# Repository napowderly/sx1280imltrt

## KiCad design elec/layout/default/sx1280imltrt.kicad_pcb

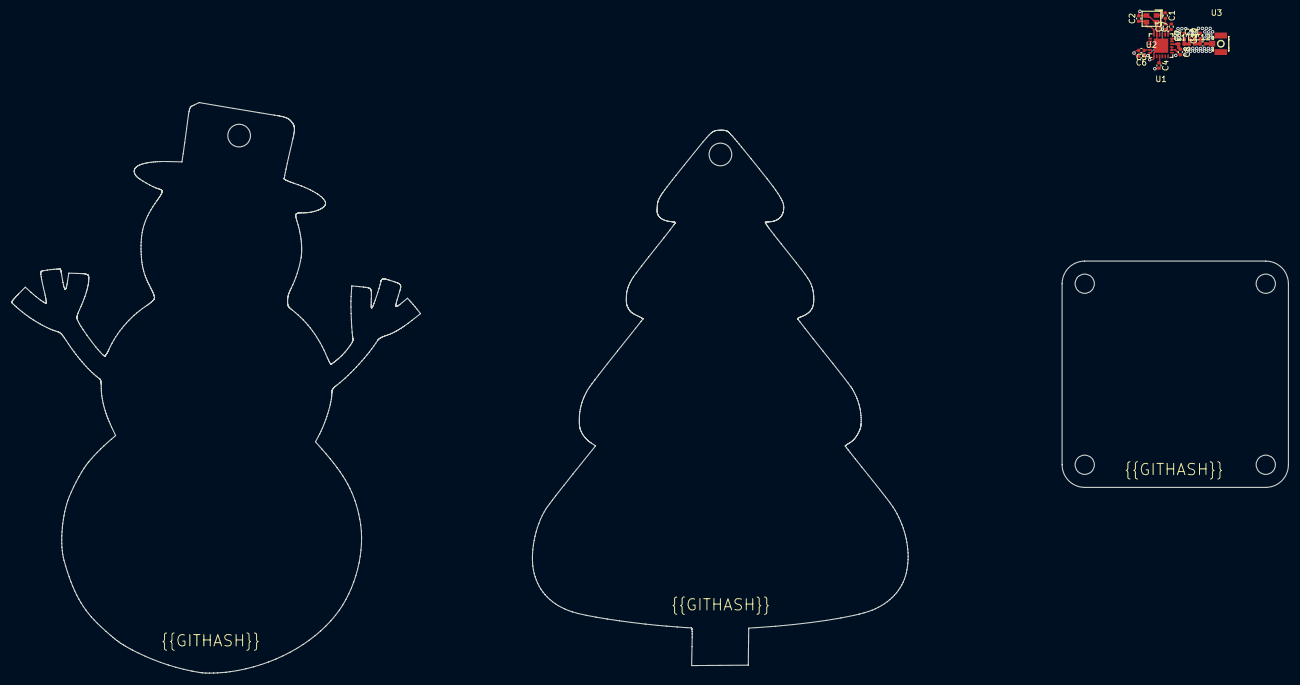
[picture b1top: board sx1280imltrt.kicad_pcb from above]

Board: 2 copper layers, 17 parts (0 on the bottom side), 10 nets.

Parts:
C1, C2: 50V 11pF C0G ±5% 0402 Multilayer Ceramic Capacito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; C0402
C3: 10V 470nF X5R ±10% 0402 Multilayer Ceramic Capaci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; C0402
C4, C5: Multilayer Ceramic Capacitors MLCC - SMD/SMT 100n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; C0402
C6, C7: 50V 10nF X7R ±10% 0402 Multilayer Ceramic Capacit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; C0402
C8, C9, C10, C11: 50V 1pF C0G 0402 Multilayer Ceramic Capacitors ML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; C0402
C12: 50V 100pF C0G ±5% 0402 Multilayer Ceramic Capacit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; C0402
L1, L2: L0402
U1: QFN-24_L4.0-W4.0-P0.50-BL-EP2.6
U2: OSC-SMD_4P-L2.0-W1.6-BL
U3: IPEX-SMD_BWIPX-1-001E

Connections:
gnd: C1.2, C2.2, C3.2, C4.2, C5.2, C6.2, C7.2, C8.2, C9.2, C10.2, U1.5, U1.13, U1.20, U1.21, U1.23, U1.24, U1.25, U2.2, U2.4, U3.2, U3.3
gnd-3: C12.2, U3.1
io: C8.1, L1.1, U1.22
vcc: C7.1, U1.1
vcc-1: C3.1, C6.1, U1.2, U1.12
vcc-2: C4.1, C5.1, U1.11, U1.15
vcc-4: C9.1, C11.1, L1.2, L2.1
vcc-5: C10.1, C11.2, C12.1, L2.2
xta: C1.1, U1.4, U2.1
xtb: C2.1, U1.6, U2.3

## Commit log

2024-02-16 Configure project
2024-02-17 initial design
2024-02-17 layout
